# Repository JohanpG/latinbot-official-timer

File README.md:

# latinbot-official-timer
Project on processing and arduino for the official timer used in the international robotics tournament LATINBOT https://twitter.com/torneolatinbot?lang=en

# The Sensor

The sensor used was based on a IR Sender and receiver. The PWM on the sender was controller by an Arduino Micro and the Receiver used an Arduino Uno with was conecter via serial to the PC where the processing Application was being executed. Both schematics for the sender and receiver are provided in this repository.

## Sender

[Schematics Here](https://github.com/JohanpG/latinbot-official-timer/blob/master/Schematics/sender.pdf)

## Receiver

[Schematics Here](https://github.com/JohanpG/latinbot-official-timer/blob/master/Schematics/receiver.pdf)
  
# Video

https://www.youtube.com/watch?v=m9lWtLH9l_A&t=2m27s

# Author

**By: Johan Porras (JohanpG)**

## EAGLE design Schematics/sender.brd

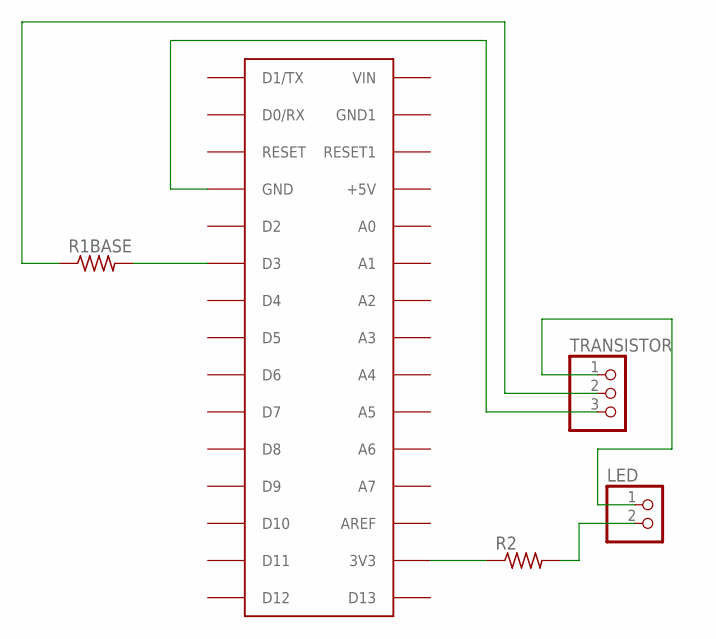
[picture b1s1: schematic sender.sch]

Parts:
LED: PINHD-1X2; 1X02
R1BASE, R2: R-US_0207/12; 0207/12
TRANSISTOR: PINHD-1X3; 1X03
U$1: ARDUINONANO; PDIP-32

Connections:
unnamed: TRANSISTOR.3, U$1.GND
unnamed: LED.1, TRANSISTOR.1
unnamed: LED.2, R2.2
unnamed: R2.1, U$1.3V3
unnamed: R1BASE.1, TRANSISTOR.2
unnamed: R1BASE.2, U$1.D3

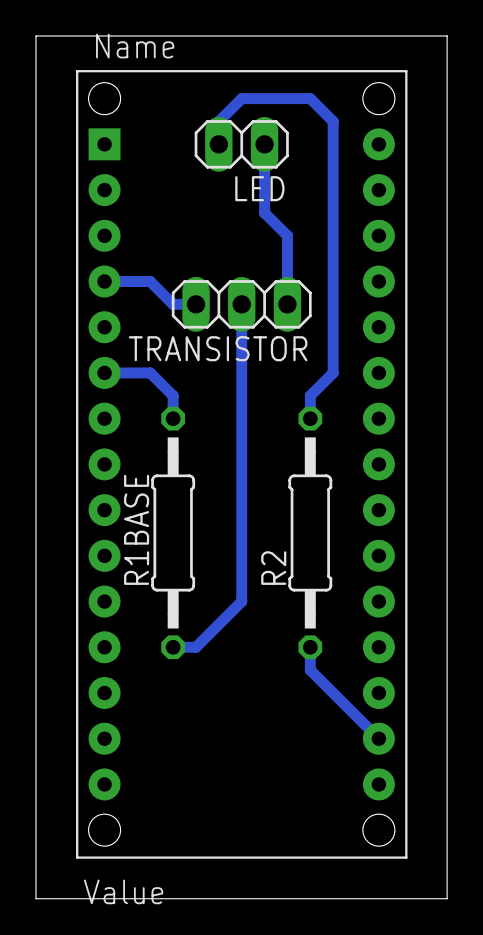
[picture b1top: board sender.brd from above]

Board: 2 copper layers, 22.8 x 47.9 mm, 5 parts (0 on the bottom side), 6 nets.

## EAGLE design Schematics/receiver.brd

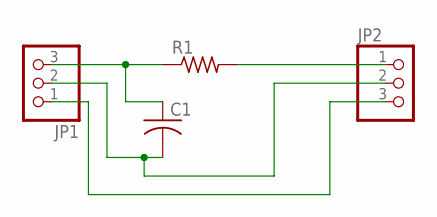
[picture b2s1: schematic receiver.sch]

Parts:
C1: C-US025-030X050; C025-030X050
JP1, JP2: PINHD-1X3; 1X03
R1: R-US_0207/12; 0207/12

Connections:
unnamed: C1.1, JP1.3, R1.1
unnamed: JP2.1, R1.2
unnamed: C1.2, JP1.2, JP2.2
unnamed: JP1.1, JP2.3

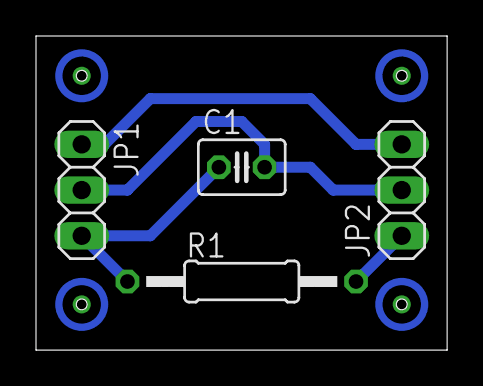
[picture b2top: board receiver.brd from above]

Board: 2 copper layers, 22.8 x 17.4 mm, 4 parts (0 on the bottom side), 4 nets.

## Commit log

2019-10-16 Loaded local files
2019-11-15 Updated
    User rising to stand aonme
